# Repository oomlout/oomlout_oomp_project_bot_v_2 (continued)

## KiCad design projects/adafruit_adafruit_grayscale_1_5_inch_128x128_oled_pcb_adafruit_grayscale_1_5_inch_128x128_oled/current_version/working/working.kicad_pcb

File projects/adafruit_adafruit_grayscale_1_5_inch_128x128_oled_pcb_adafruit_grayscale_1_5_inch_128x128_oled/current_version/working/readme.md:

# adafruit_grayscale_1_5_inch_128x128_oled_pcb
 
## summary 
* id: adafruit_adafruit_grayscale_1_5_inch_128x128_oled_pcb_adafruit_grayscale_1_5_inch_128x128_oled
* user: adafruit
* name: adafruit_grayscale_1_5_inch_128x128_oled_pcb
* board: adafruit_grayscale_1_5_inch_128x128_oled
* repo: https://github.com/adafruit/Adafruit-Grayscale-1.5-inch-128x128-OLED-PCB

* src_file_repo_sch: 
* src_file_repo_sch_link: https://github.com/adafruit/Adafruit-Grayscale-1.5-inch-128x128-OLED-PCB/tree/main/
* full details link: https://github.com/oomlout/oomlout_oomp_project_bot_v_2/tree/main/projects/adafruit_adafruit_grayscale_1_5_inch_128x128_oled_pcb_adafruit_grayscale_1_5_inch_128x128_oled/current_version/working  

## schematic  
  
[schematic (pdf)](working_schematic.pdf) 

## pcb  

[board (pdf)](working.pdf)  

## working_bom
| Id | Designator | Footprint | Quantity | Designation | Supplier and ref |  | None | 
| --- | --- | --- | --- | --- | --- | --- | --- | 
| 1 | D4,D5,D3 | SOD-323 | 3 | 1N4148 |  |  | [''] | 
| 2 | SJ1,SJ2 | SOLDERJUMPER_CLOSEDWIRE | 2 |  |  |  | [''] | 
| 3 | C1,C8 | 0603-NO | 2 | 0.1uF |  |  | [''] | 
| 4 | R2,R3 | RESPACK_4X0603 | 2 | 10K |  |  | [''] | 
| 5 | U$25 | PCBFEAT-REV-040 | 1 |  |  |  | [''] | 
| 6 | Q2 | SOT363 | 1 | BSS138 |  |  | [''] | 
| 7 | U$20,U$31 | STEMMAQT | 2 |  |  |  | [''] | 
| 8 | FID3,FID4 | FIDUCIAL_1MM | 2 | FIDUCIAL_1MM |  |  | [''] | 
| 9 | C16,C3,C14,C7,C2,C15 | 0805-NO | 6 | 10uF |  |  | [''] | 
| 10 | C17 | 0603-NO | 1 | 1uF |  |  | [''] | 
| 11 | R9 | 0603-NO | 1 | 390K |  |  | [''] | 
| 12 | U$1,U$21,U$17,U$19 | MOUNTINGHOLE_2.5_PLATED | 4 | MOUNTINGHOLE2.5 |  |  | [''] | 
| 13 | D2 | SOD-123 | 1 | MBR120 |  |  | [''] | 
| 14 | R7,R1 | 0603-NO | 2 | 10K |  |  | [''] | 
| 15 | U2 | SOT23-5 | 1 | AP2112K-3.3 |  |  | [''] | 
| 16 | JP2 | 1X08_ROUND_70 | 1 |  |  |  | [''] | 
| 17 | IC5 | SOT23 | 1 | APX803 |  |  | [''] | 
| 18 | R6 | 0603-NO | 1 | 100K |  |  | [''] | 
| 19 | CONN4,CONN1 | JST_SH4 | 2 | STEMMA_I2C_QT |  |  | [''] | 
| 20 | U3 | SOT23-5@1 | 1 | FAN5331SX |  |  | [''] | 
| 21 | D1 | CHIPLED_0603_NOOUTLINE | 1 | GREEN |  |  | [''] | 
| 22 | U$8 | ADAFRUIT_5MM | 1 |  |  |  | [''] | 
| 23 | SJ3 | SOLDERJUMPER_ARROW_NOPASTE | 1 |  |  |  | [''] | 
| 24 | L1 | INDUCTOR_1007 | 1 | 10uH |  |  | [''] | 
| 25 | X1 | OLED_1.5IN_128X128MONO | 1 | OLED_1.5_128X128_MONO |  |  | [''] | 

## bom_schematic
| Ref | Qnty | Value | Cmp name | Footprint | Description | Vendor | DNP | 
| --- | --- | --- | --- | --- | --- | --- | --- | 
| C1, C8 | 2 | 0.1uF | CAP_CERAMIC0603_NO | working:0603-NO |  |  |  | 
| C2, C3, C7, C14, C15, C16 | 6 | 10uF | CAP_CERAMIC0805-NOOUTLINE | working:0805-NO |  |  |  | 
| C17 | 1 | 1uF | CAP_CERAMIC0603_NO | working:0603-NO |  |  |  | 
| CONN1, CONN4 | 2 | STEMMA_I2C_QT | STEMMA_I2C_QT | working:JST_SH4 |  |  |  | 
| D1 | 1 | GREEN | LED0603_NOOUTLINE | working:CHIPLED_0603_NOOUTLINE |  |  |  | 
| D2 | 1 | MBR120 | DIODESOD-123 | working:SOD-123 |  |  |  | 
| D3, D4, D5 | 3 | 1N4148 | DIODESOD-323 | working:SOD-323 |  |  |  | 
| FID3, FID4 | 2 | FIDUCIAL_1MM | FIDUCIAL_1MM | working:FIDUCIAL_1MM |  |  |  | 
| IC5 | 1 | APX803 | AXP083-SAG | working:SOT23 |  |  |  | 
| JP2 | 1 | HEADER-1X870MIL | HEADER-1X870MIL | working:1X08_ROUND_70 |  |  |  | 
| L1 | 1 | 10uH | INDUCTOR | working:INDUCTOR_1007 |  |  |  | 
| Q2 | 1 | BSS138 | MOSFET-N_DUAL | working:SOT363 |  |  |  | 
| R1, R7 | 2 | 10K | RESISTOR_0603_NOOUT | working:0603-NO |  |  |  | 
| R2, R3 | 2 | 10K | RESISTOR_4PACK | working:RESPACK_4X0603 |  |  |  | 
| R6 | 1 | 100K | RESISTOR_0603_NOOUT | working:0603-NO |  |  |  | 
| R9 | 1 | 390K | RESISTOR_0603_NOOUT | working:0603-NO |  |  |  | 
| SJ1, SJ2 | 2 | SOLDERJUMPERCLOSED | SOLDERJUMPERCLOSED | working:SOLDERJUMPER_CLOSEDWIRE |  |  |  | 
| SJ3 | 1 | SOLDERJUMPER | SOLDERJUMPER | working:SOLDERJUMPER_ARROW_NOPASTE |  |  |  | 
| U2 | 1 | AP2112K-3.3 | VREG_SOT23-5 | working:SOT23-5 |  |  |  | 
| U3 | 1 | FAN5331SX | FAN5331 | working:SOT23-5@1 |  |  |  | 
| U$1, U$17, U$19, U$21 | 4 | MOUNTINGHOLE2.5 | MOUNTINGHOLE2.5 | working:MOUNTINGHOLE_2.5_PLATED |  |  |  | 
| X1 | 1 | OLED_1.5_128X128_MONO | OLED_1.5_128X128_MONO | working:OLED_1.5IN_128X128MONO |  |  |  | 

## mounting_holes
| x | y | package | value | ref | size | 
| --- | --- | --- | --- | --- | --- | 
| 0.0 | 41.91 | MOUNTINGHOLE_2.5_PLATED | MOUNTINGHOLE2.5 | U$1 | m3 | 
| 30.48 | 41.91 | MOUNTINGHOLE_2.5_PLATED | MOUNTINGHOLE2.5 | U$17 | m3 | 
| 0.0 | 0.0 | MOUNTINGHOLE_2.5_PLATED | MOUNTINGHOLE2.5 | U$19 | m3 | 
| 30.48 | 0.0 | MOUNTINGHOLE_2.5_PLATED | MOUNTINGHOLE2.5 | U$21 | m3 |

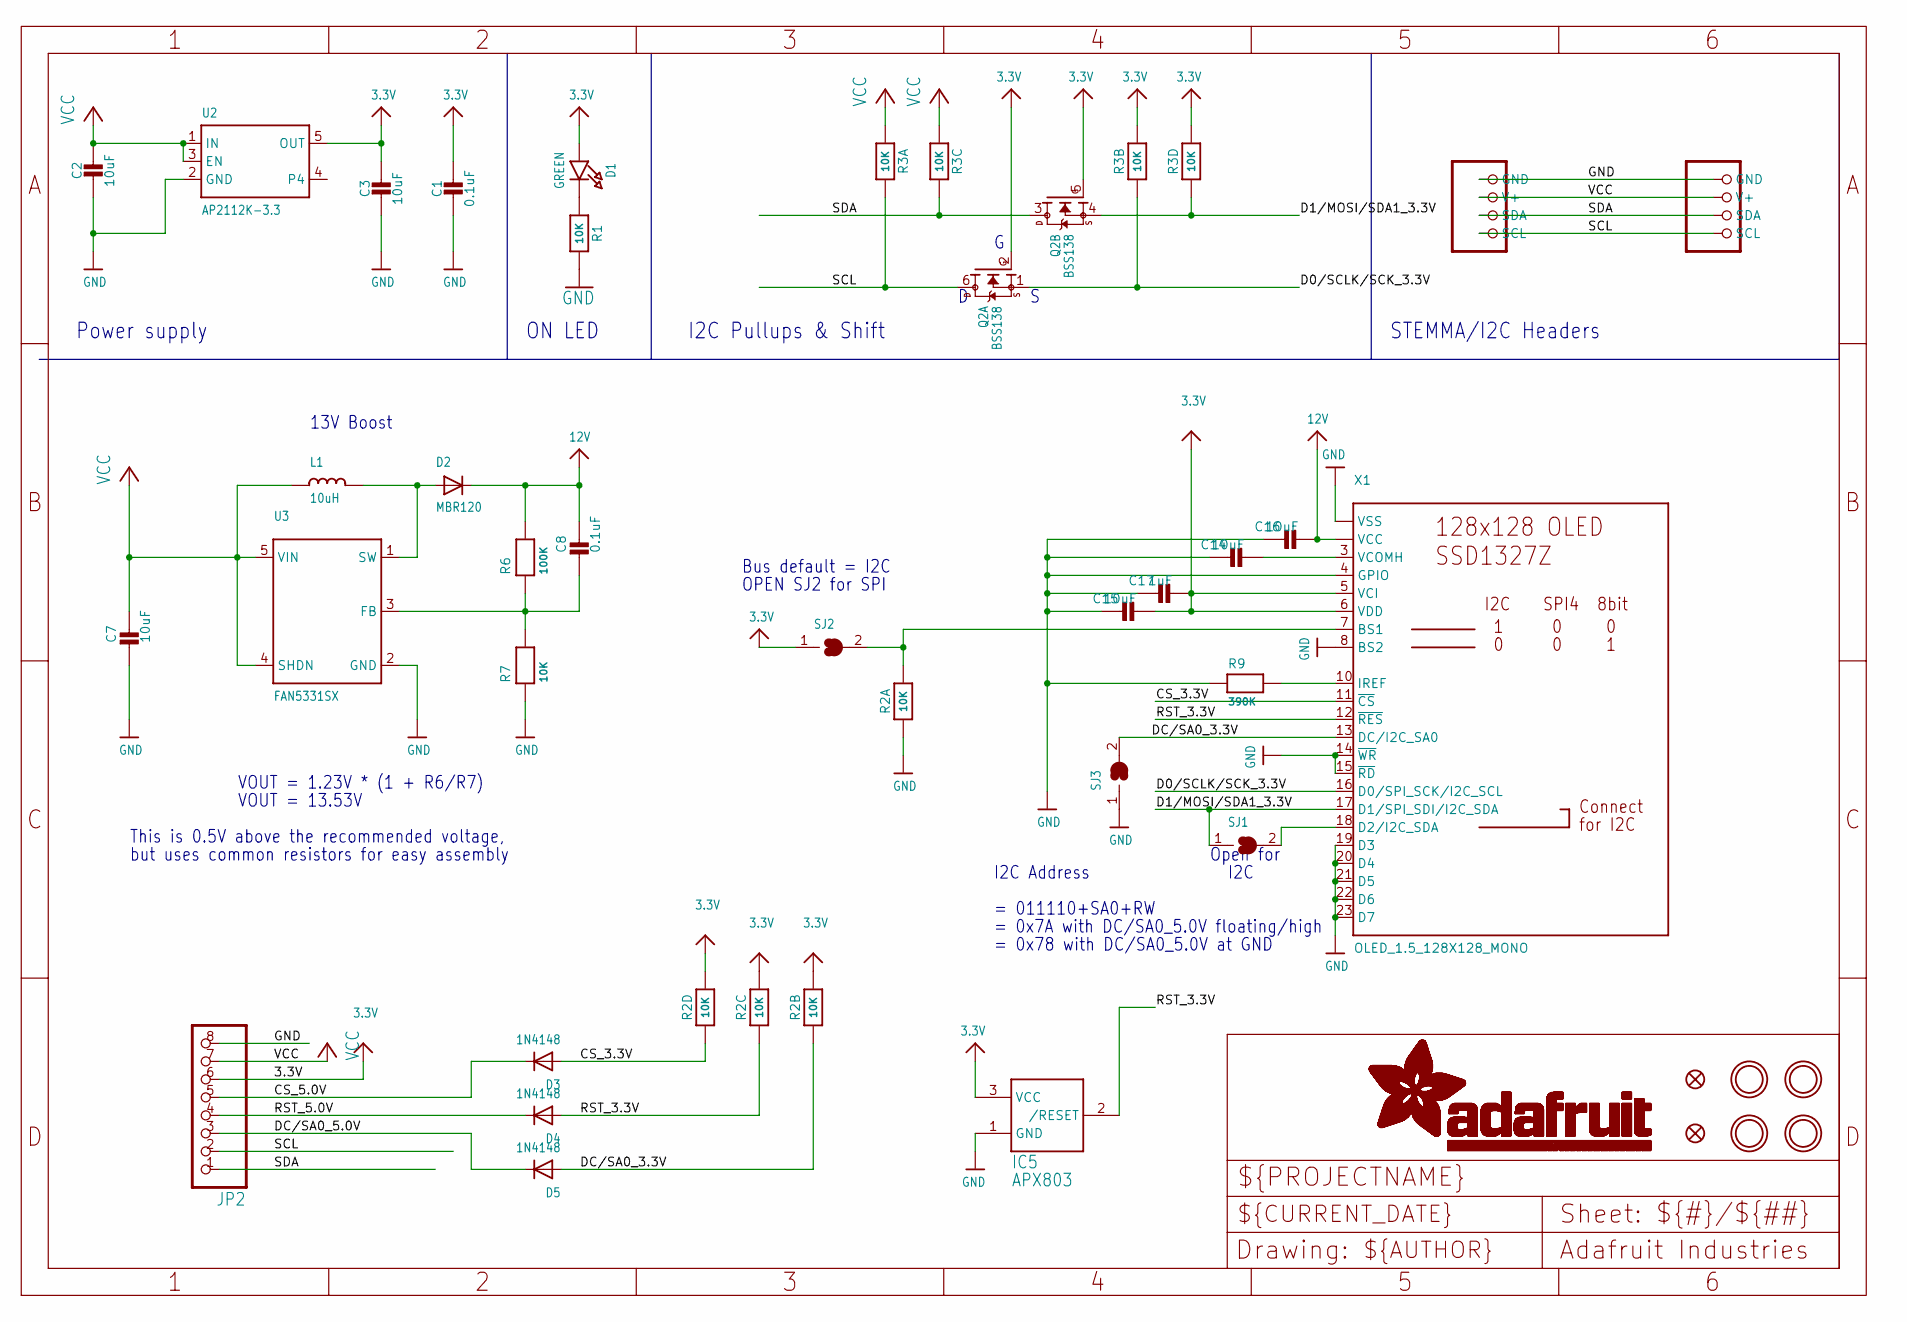
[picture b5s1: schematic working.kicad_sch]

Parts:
C1, C8: 0.1uF; 0603-NO
C2, C3, C7, C14, C15, C16: 10uF; 0805-NO
C17: 1uF; 0603-NO
CONN1, CONN4: STEMMA_I2C_QT; JST_SH4
D1: GREEN; CHIPLED_0603_NOOUTLINE
D2: MBR120; SOD-123
D3, D4, D5: 1N4148; SOD-323
FID3, FID4: FIDUCIAL_1MM
IC5: APX803; SOT23
JP2: HEADER-1X870MIL; 1X08_ROUND_70
L1: 10uH; INDUCTOR_1007
Q2: BSS138; SOT363
R1, R7: 10K; 0603-NO
R2, R3: 10K; RESPACK_4X0603
R6: 100K; 0603-NO
R9: 390K; 0603-NO
SJ1, SJ2: SOLDERJUMPERCLOSED; SOLDERJUMPER_CLOSEDWIRE
SJ3: SOLDERJUMPER; SOLDERJUMPER_ARROW_NOPASTE
U2: AP2112K-3.3; SOT23-5
U3: FAN5331SX; SOT23-5@1
U$1, U$17, U$19, U$21: MOUNTINGHOLE2.5; MOUNTINGHOLE_2.5_PLATED
X1: OLED_1.5_128X128_MONO; OLED_1.5IN_128X128MONO

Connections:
3.3V: C1.1, C3.1, C15.2, C17.2, D1.A, IC5.3 (VCC), JP2.6, Q2.2 (G), Q2.5 (G), R2.5 (2), R2.6 (2), R2.7 (2), R3.2 (1), R3.4 (1), SJ2.1, U2.5 (OUT), X1.5 (VCI), X1.6 (VDD)
12V: C8.1, C16.2, D2.C, R6.2, X1.2 (VCC), X1.24 (VCC)
CS_3.3V: D3.A, R2.4 (1), X1.11 (~CS)
CS_5.0V: D3.C, JP2.5
D0/SCLK/SCK_3.3V: Q2.1 (S), R3.7 (2), X1.16 (D0/SPI_SCK/I2C_SCL)
D1/MOSI/SDA1_3.3V: Q2.4 (S), R3.5 (2), SJ1.1, X1.17 (D1/SPI_SDI/I2C_SDA)
DC/SA0_3.3V: D5.A, R2.2 (1), SJ3.2, X1.13 (DC/I2C_SA0)
DC/SA0_5.0V: D5.C, JP2.3
GND: C1.2, C2.2, C3.2, C7.2, C14.1, C15.1, C16.1, C17.1, CONN1.1 (GND), CONN4.1 (GND), IC5.1 (GND), JP2.8, R1.2, R2.1, R7.1, R9.1, SJ3.1, U2.2 (GND), U3.2 (GND), X1.1 (VSS), X1.4 (GPIO), X1.8 (BS2), X1.9 (VSS), X1.14 (~WR), X1.15 (~RD), X1.19 (D3), X1.20 (D4), X1.21 (D5), X1.22 (D6), X1.23 (D7), X1.25 (VSS)
unnamed: D1.C, R1.1
unnamed: D2.A, L1.P$2 (2), U3.1 (SW)
unnamed: C8.2, R6.1, R7.2, U3.3 (FB)
unnamed: R2.8 (2), SJ2.2, X1.7 (BS1)
unnamed: R9.2, X1.10 (IREF)
unnamed: C14.2, X1.3 (VCOMH)
unnamed: SJ1.2, X1.18 (D2/I2C_SDA)
RST_3.3V: D4.A, IC5.2 (/RESET), R2.3 (1), X1.12 (~RES)
RST_5.0V: D4.C, JP2.4
SCL: CONN1.4 (SCL), CONN4.4 (SCL), JP2.2, Q2.6 (D), R3.8 (2)
SDA: CONN1.3 (SDA), CONN4.3 (SDA), JP2.1, Q2.3 (D), R3.6 (2)
VCC: C2.1, C7.1, CONN1.2 (V+), CONN4.2 (V+), JP2.7, L1.P$1 (1), R3.1, R3.3 (1), U2.1 (IN), U2.3 (EN), U3.4 (SHDN), U3.5 (VIN)

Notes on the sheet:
I2C
Open for
= 0x7A with DC/SA0_5.0V floating/high
This is 0.5V above the recommended voltage,
ON LED
but uses common resistors for easy assembly
I2C Pullups & Shift
= 011110+SA0+RW
= 0x78 with DC/SA0_5.0V at GND
Bus default = I2C
13V Boost
OPEN SJ2 for SPI
STEMMA/I2C Headers
VOUT = 13.53V
I2C Address
Power supply
VOUT = 1.23V * (1 + R6/R7)

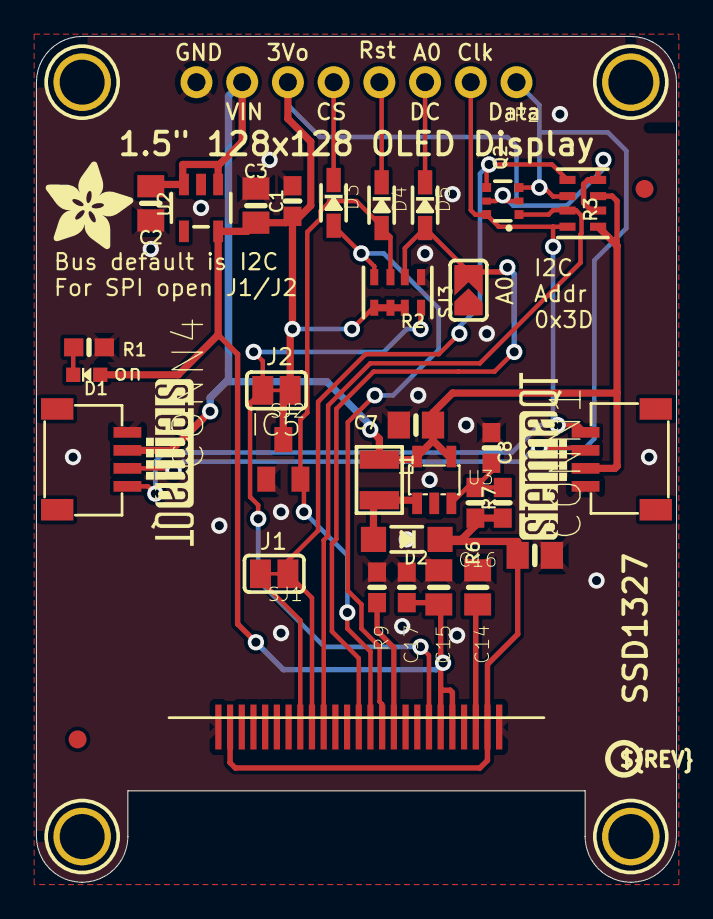
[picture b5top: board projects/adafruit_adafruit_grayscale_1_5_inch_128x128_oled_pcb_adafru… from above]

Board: 2 copper layers, 35.6 x 47.0 mm, 42 parts (1 on the bottom side), 21 nets.

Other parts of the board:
U$8: ADAFRUIT_5MM
U$20, U$31: STEMMAQT
U$25: PCBFEAT-REV-040

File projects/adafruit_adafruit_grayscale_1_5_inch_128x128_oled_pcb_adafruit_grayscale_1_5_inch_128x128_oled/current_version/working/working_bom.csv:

"Id";"Designator";"Footprint";"Quantity";"Designation";"Supplier and ref";
1;"D4,D5,D3";"SOD-323";3;"1N4148";;;
2;"SJ1,SJ2";"SOLDERJUMPER_CLOSEDWIRE";2;"";;;
3;"C1,C8";"0603-NO";2;"0.1uF";;;
4;"R2,R3";"RESPACK_4X0603";2;"10K";;;
5;"U$25";"PCBFEAT-REV-040";1;"";;;
6;"Q2";"SOT363";1;"BSS138";;;
7;"U$20,U$31";"STEMMAQT";2;"";;;
8;"FID3,FID4";"FIDUCIAL_1MM";2;"FIDUCIAL_1MM";;;
9;"C16,C3,C14,C7,C2,C15";"0805-NO";6;"10uF";;;
10;"C17";"0603-NO";1;"1uF";;;
11;"R9";"0603-NO";1;"390K";;;
12;"U$1,U$21,U$17,U$19";"MOUNTINGHOLE_2.5_PLATED";4;"MOUNTINGHOLE2.5";;;
13;"D2";"SOD-123";1;"MBR120";;;
14;"R7,R1";"0603-NO";2;"10K";;;
15;"U2";"SOT23-5";1;"AP2112K-3.3";;;
16;"JP2";"1X08_ROUND_70";1;"";;;
17;"IC5";"SOT23";1;"APX803";;;
18;"R6";"0603-NO";1;"100K";;;
19;"CONN4,CONN1";"JST_SH4";2;"STEMMA_I2C_QT";;;
20;"U3";"SOT23-5@1";1;"FAN5331SX";;;
21;"D1";"CHIPLED_0603_NOOUTLINE";1;"GREEN";;;
22;"U$8";"ADAFRUIT_5MM";1;"";;;
23;"SJ3";"SOLDERJUMPER_ARROW_NOPASTE";1;"";;;
24;"L1";"INDUCTOR_1007";1;"10uH";;;
25;"X1";"OLED_1.5IN_128X128MONO";1;"OLED_1.5_128X128_MONO";;;

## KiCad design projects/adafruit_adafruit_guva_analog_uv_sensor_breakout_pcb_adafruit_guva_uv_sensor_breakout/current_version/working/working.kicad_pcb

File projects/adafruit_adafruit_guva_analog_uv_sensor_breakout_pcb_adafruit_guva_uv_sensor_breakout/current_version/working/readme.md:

# adafruit_guva_analog_uv_sensor_breakout_pcb
 
## summary 
* id: adafruit_adafruit_guva_analog_uv_sensor_breakout_pcb_adafruit_guva_uv_sensor_breakout
* user: adafruit
* name: adafruit_guva_analog_uv_sensor_breakout_pcb
* board: adafruit_guva_uv_sensor_breakout
* repo: https://github.com/adafruit/Adafruit-GUVA-Analog-UV-Sensor-Breakout-PCB

* src_file_repo_sch: 
* src_file_repo_sch_link: https://github.com/adafruit/Adafruit-GUVA-Analog-UV-Sensor-Breakout-PCB/tree/master/
* full details link: https://github.com/oomlout/oomlout_oomp_project_bot_v_2/tree/main/projects/adafruit_adafruit_guva_analog_uv_sensor_breakout_pcb_adafruit_guva_uv_sensor_breakout/current_version/working  

## schematic  
  
[schematic (pdf)](working_schematic.pdf) 

## pcb  

[board (pdf)](working.pdf)  

## working_bom
| Id | Designator | Footprint | Quantity | Designation | Supplier and ref |  | None | 
| --- | --- | --- | --- | --- | --- | --- | --- | 
| 1 | U1 | SOT23-5 | 1 | MCP6001 |  |  | [''] | 
| 2 | R1 | 0805-NO | 1 | 1M |  |  | [''] | 
| 3 | JP2 | 1X03-CLEANBIG | 1 |  |  |  | [''] | 
| 4 | C2,C1 | 0805-NO | 2 | 0.1uF |  |  | [''] | 
| 5 | U2 | GUVA-S12SD | 1 | GUVA-S12SD |  |  | [''] | 
| 6 | U$7,U$8 | ADAFRUIT_2.5MM | 2 |  |  |  | [''] | 
| 7 | FID1,FID2 | FIDUCIAL_1MM | 2 | FIDUCIAL" |  |  | [''] | 
| 8 | U$6 | MOUNTINGHOLE_2.5_PLATED | 1 | MOUNTINGHOLE2.5 |  |  | [''] | 
| 9 | R2 | 0805-NO | 1 | 3.3K |  |  | [''] | 
| 10 | R3 | 0805-NO | 1 | 1K |  |  | [''] | 

## bom_schematic
| Ref | Qnty | Value | Cmp name | Footprint | Description | Vendor | DNP | 
| --- | --- | --- | --- | --- | --- | --- | --- | 
| C1, C2 | 2 | 0.1uF | CAP_CERAMIC0805-NOOUTLINE | working:0805-NO |  |  |  | 
| FID1, FID2 | 2 | FIDUCIAL"" | FIDUCIAL{dblquote}{dblquote} | working:FIDUCIAL_1MM |  |  |  | 
| JP2 | 1 | PINHD-1X3CB | PINHD-1X3CB | working:1X03-CLEANBIG |  |  |  | 
| R1 | 1 | 1M | RESISTOR0805_NOOUTLINE | working:0805-NO |  |  |  | 
| R2 | 1 | 3.3K | RESISTOR0805_NOOUTLINE | working:0805-NO |  |  |  | 
| R3 | 1 | 1K | RESISTOR0805_NOOUTLINE | working:0805-NO |  |  |  | 
| U1 | 1 | MCP6001 | OPAMP_SINGLESOT235 | working:SOT23-5 |  |  |  | 
| U2 | 1 | GUVA-S12SD | UV_GUVA-S12SD | working:GUVA-S12SD |  |  |  | 
| U$6 | 1 | MOUNTINGHOLE2.5 | MOUNTINGHOLE2.5 | working:MOUNTINGHOLE_2.5_PLATED |  |  |  | 

## mounting_holes
| x | y | package | value | ref | size | 
| --- | --- | --- | --- | --- | --- | 
| 0.0 | 0.0 | MOUNTINGHOLE_2.5_PLATED | MOUNTINGHOLE2.5 | U$6 | m3 |

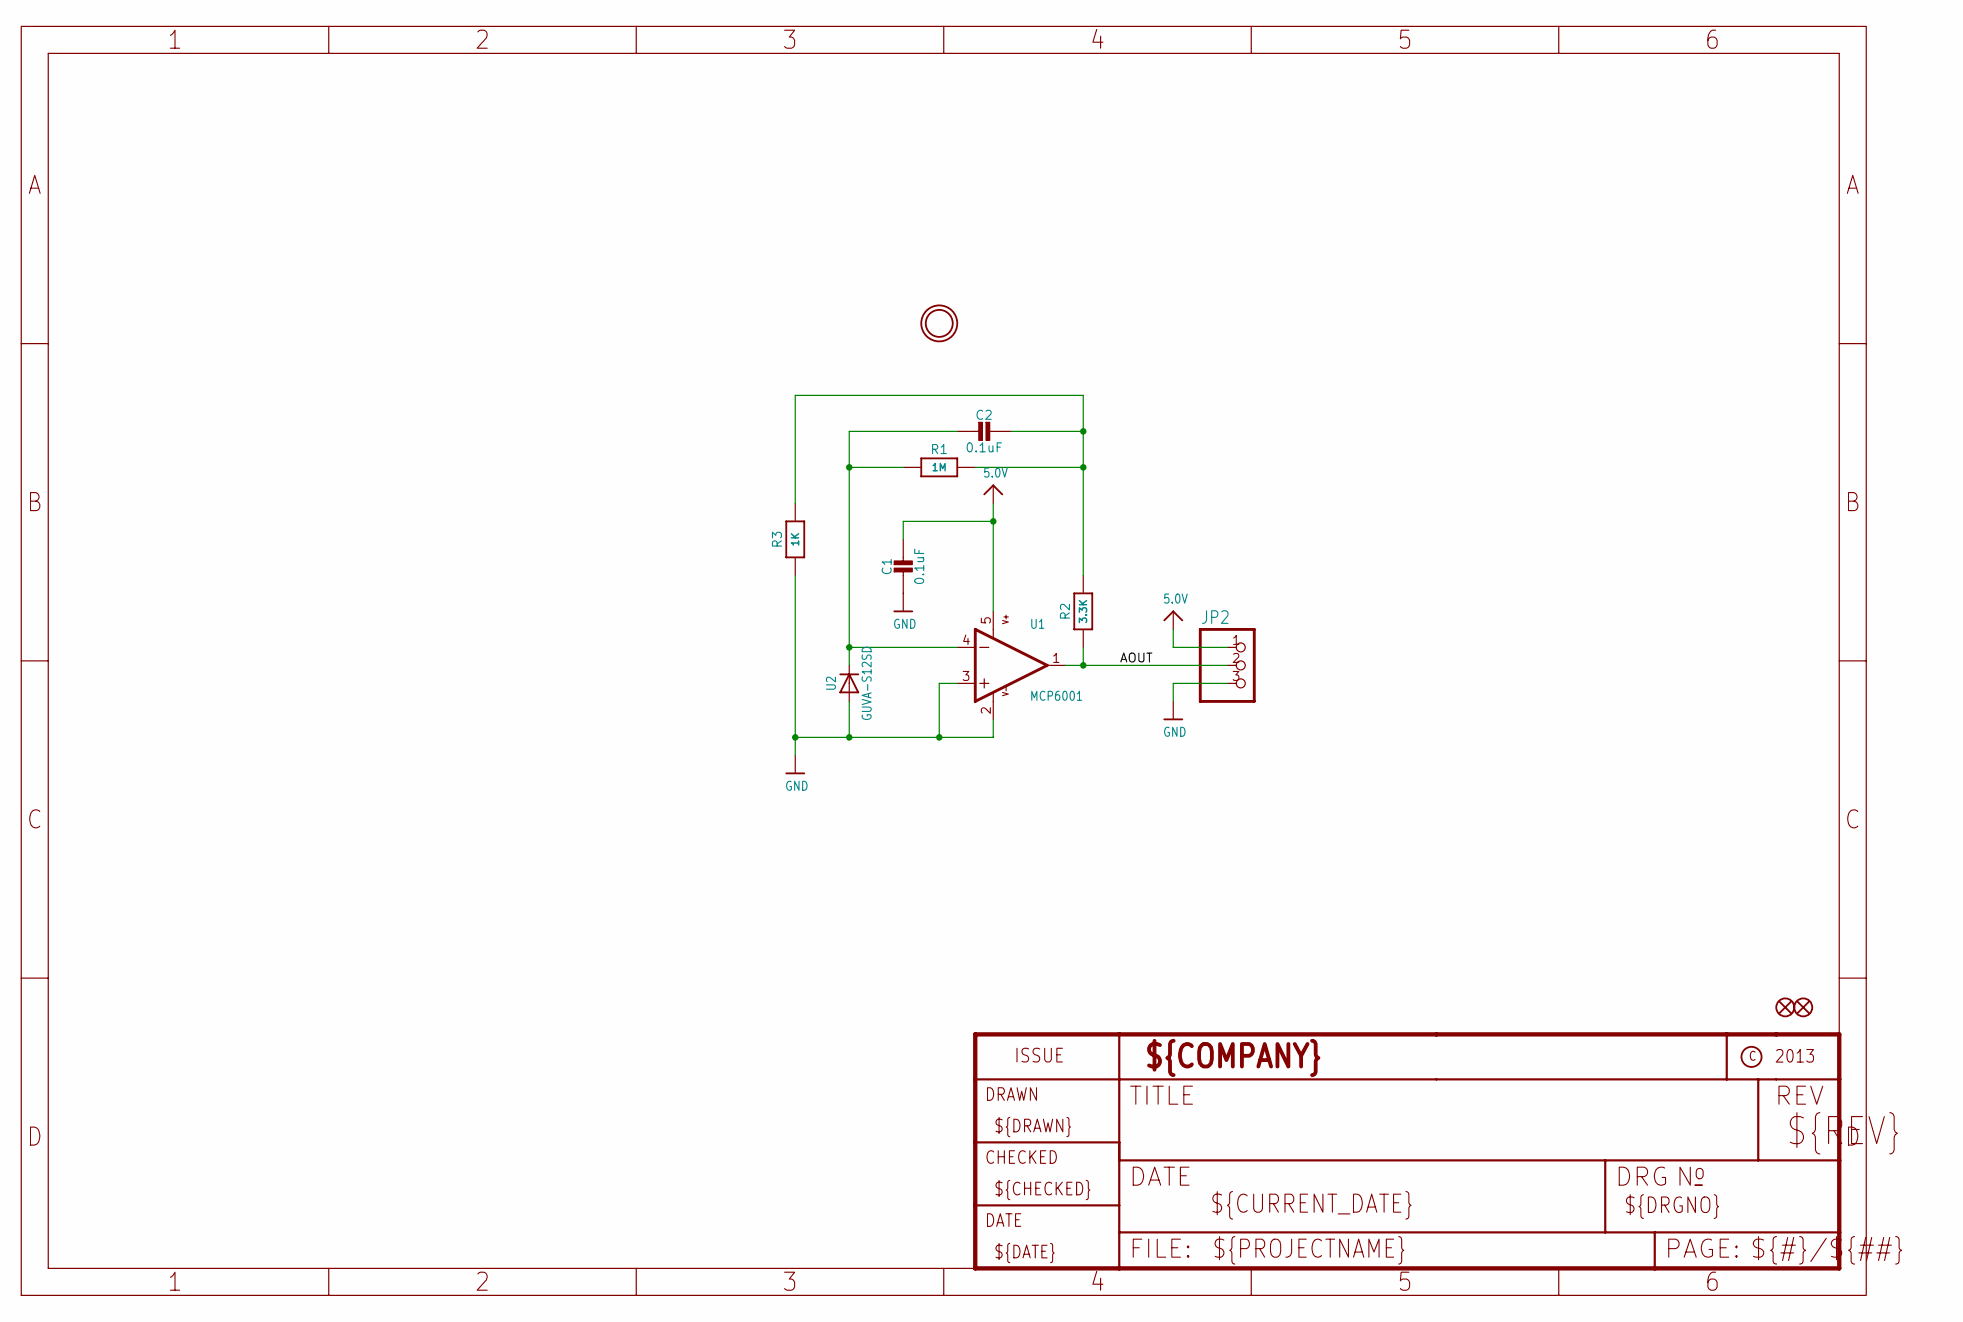
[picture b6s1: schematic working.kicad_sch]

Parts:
C1, C2: 0.1uF; 0805-NO
FID1, FID2: FIDUCIAL""; FIDUCIAL_1MM
JP2: PINHD-1X3CB; 1X03-CLEANBIG
R1: 1M; 0805-NO
R2: 3.3K; 0805-NO
R3: 1K; 0805-NO
U1: MCP6001; SOT23-5
U2: GUVA-S12SD
U$6: MOUNTINGHOLE2.5; MOUNTINGHOLE_2.5_PLATED

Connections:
5.0V: C1.1, JP2.1, U1.5 (V+)
AOUT: JP2.2, R2.1, U1.1 (OUT)
GND: C1.2, JP2.3, R3.1, U1.2 (V-), U1.3 (+IN), U2.A
unnamed: C2.1, R1.2, R2.2, R3.2
unnamed: C2.2, R1.1, U1.4 (-IN), U2.K (C)

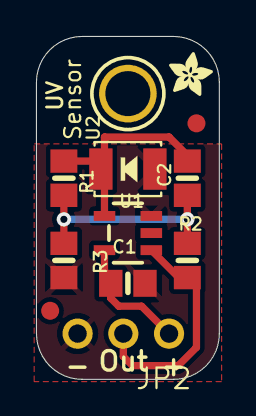
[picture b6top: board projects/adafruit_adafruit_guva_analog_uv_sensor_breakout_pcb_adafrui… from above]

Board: 2 copper layers, 10.2 x 19.0 mm, 13 parts (1 on the bottom side), 5 nets.

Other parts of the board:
U$7, U$8: ADAFRUIT_2.5MM

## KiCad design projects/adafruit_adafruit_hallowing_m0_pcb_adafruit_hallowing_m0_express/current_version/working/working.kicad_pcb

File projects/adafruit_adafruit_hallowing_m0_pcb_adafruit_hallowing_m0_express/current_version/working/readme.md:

# adafruit_hallowing_m0_pcb
 
## summary 
* id: adafruit_adafruit_hallowing_m0_pcb_adafruit_hallowing_m0_express
* user: adafruit
* name: adafruit_hallowing_m0_pcb
* board: adafruit_hallowing_m0_express
* repo: https://github.com/adafruit/Adafruit-Hallowing-M0-PCB

* src_file_repo_sch: 
* src_file_repo_sch_link: https://github.com/adafruit/Adafruit-Hallowing-M0-PCB/tree/master/
* full details link: https://github.com/oomlout/oomlout_oomp_project_bot_v_2/tree/main/projects/adafruit_adafruit_hallowing_m0_pcb_adafruit_hallowing_m0_express/current_version/working  

## schematic  
  
[schematic (pdf)](working_schematic.pdf) 

## pcb  

[board (pdf)](working.pdf)  

## working_bom
| Id | Designator | Footprint | Quantity | Designation | Supplier and ref |  | None | 
| --- | --- | --- | --- | --- | --- | --- | --- | 
| 1 | D1,D2 | SOD-323 | 2 | 3.6V |  |  | [''] | 
| 2 | R3,R8 | 0603-NO | 2 | 10K |  |  | [''] | 
| 3 | U1 | SOIC8_208MIL | 1 | 2MB Flash |  |  | [''] | 
| 4 | @HOLE3,@HOLE1,@HOLE2,@HOLE0 |  | 4 |  |  |  | [''] | 
| 5 | C9,C13,C7,C1,C4,C2,C14 | 0603-NO | 7 | 1uF |  |  | [''] | 
| 6 | R6,R5,R2 | 0603-NO | 3 | 1K |  |  | [''] | 
| 7 | MS1 | FEATHERWING_SMT_NOHOLES | 1 | FEATHERWING_SMTDUALNOHOLES |  |  | [''] | 
| 8 | LED1 | LED3535 | 1 | WS2812B3535 |  |  | [''] | 
| 9 | TP28,TP4 | PCB_ALLI | 2 | SEWTAPPCB_ALLIGATOR |  |  | [''] | 
| 10 | U2 | SOT23-5 | 1 | AP2112-3.3 |  |  | [''] | 
| 11 | U3 | SOT23-5 | 1 | MCP73831T-2ACI/OT |  |  | [''] | 
| 12 | X6 | JSTPH2 | 1 | CON_JST_PH_2PIN_MTPH2 |  |  | [''] | 
| 13 | NEOPIXEL0,PIR0 | JSTPH3 | 2 | JST PH 3 |  |  | [''] | 
| 14 | U$12 | HALLOWING_FRONT | 1 |  |  |  | [''] | 
| 15 | R13,R12 | 0603-NO | 2 | 100 |  |  | [''] | 
| 16 | C10,C15,C5 | 0805-NO | 3 | 10uF |  |  | [''] | 
| 17 | R9,R4 | RESPACK_4X0603 | 2 | 10K |  |  | [''] | 
| 18 | I2C0 | JSTPH4 | 1 | JST PH 4 |  |  | [''] | 
| 19 | Q2,Q1 | SOT23-R | 2 | DMG341 |  |  | [''] | 
| 20 | U$35,U$34 | FIDUCIAL_1MM | 2 | FIDUCIAL_1MM |  |  | [''] | 
| 21 | U4 | ALS-PT26-21C | 1 | ALS-PT21 |  |  | [''] | 
| 22 | SJ1 | SOLDERJUMPER_2WAY_OPEN_NOPASTE | 1 |  |  |  | [''] | 
| 23 | C11 | 0805_10MGAP | 1 | 10uF |  |  | [''] | 
| 24 | TP3,TP29 | PCB_ALLI_LONG | 2 | SEWTAP_ALLILONG |  |  | [''] | 
| 25 | IC4 | LGA16_3X3MM | 1 | LIS3DH |  |  | [''] | 
| 26 | U$4 | TQFN48_7MM | 1 | ATSAMD21G18_QFN |  |  | [''] | 
| 27 | R1 | RESPACK_4X0603 | 1 | 100K |  |  | [''] | 
| 28 | SW2 | EG1390 | 1 | Slide Switch |  |  | [''] | 
| 29 | CHG0 | CHIPLED_0805_NOOUTLINE | 1 | ORANGE |  |  | [''] | 
| 30 | VR2 | TRIMPOT_BOURNS_3303W | 1 | 10K trim |  |  | [''] | 
| 31 | TP5,TP1,TP2 | TESTPOINT_ROUND_1.5MM | 3 |  |  |  | [''] | 
| 32 | X3 | 4UCONN_20329_V2 | 1 | microUSB |  |  | [''] | 
| 33 | U$31,U$32 | MOUNTINGHOLE_2.5_PLATED | 2 | MOUNTINGHOLE2.5 |  |  | [''] | 
| 34 | U5 | MSOP8_0.65MM | 1 | PAM8302AASCR |  |  | [''] | 
| 35 | R7 | 0603-NO | 1 | 2.2K |  |  | [''] | 
| 36 | U$13 | 53398-0271 | 1 | CON_MOLEX_2P |  |  | [''] | 
| 37 | C3,C6 | 0805-NO | 2 | 10ÂµF |  |  | [''] | 
| 38 | Q3 | SOT23-WIDE | 1 | BSS138 |  |  | [''] | 
| 39 | C8 | 0805_10MGAP | 1 | 10ÂµF |  |  | [''] | 
| 40 | D4 | SOD-123 | 1 | MBR120 |  |  | [''] | 
| 41 | L0 | CHIPLED_0805_NOOUTLINE | 1 | RED |  |  | [''] | 
| 42 | SW1 | KMR2 | 1 | SPST_TACT-KMR2 |  |  | [''] | 
| 43 | X1 | JSTPH2 | 1 | JSTPH |  |  | [''] | 
| 44 | TFT0 | TFT_1.44IN_128_128 | 1 | DISP_LCD_ST7735_1.44IN |  |  | [''] | 
| 45 | U$8 | HALLOWING_BACK | 1 |  |  |  | [''] | 

## bom_schematic
| Ref | Qnty | Value | Cmp name | Footprint | Description | Vendor | DNP | 
| --- | --- | --- | --- | --- | --- | --- | --- | 
| C1, C2, C4, C7, C9, C13, C14 | 7 | 1uF | CAP_CERAMIC0603_NO | working:0603-NO |  |  |  | 
| C3, C6 | 2 | 10ÂµF | CAP_CERAMIC0805-NOOUTLINE | working:0805-NO |  |  |  | 
| C5, C10, C15 | 3 | 10uF | CAP_CERAMIC0805-NOOUTLINE | working:0805-NO |  |  |  | 
| C8 | 1 | 10ÂµF | CAP_CERAMIC0805_10MGAP | working:0805_10MGAP |  |  |  | 
| C11 | 1 | 10uF | CAP_CERAMIC0805_10MGAP | working:0805_10MGAP |  |  |  | 
| CHG0 | 1 | ORANGE | LED0805_NOOUTLINE | working:CHIPLED_0805_NOOUTLINE |  |  |  | 
| D1, D2 | 2 | 3.6V | DIODE-ZENERSOD323 | working:SOD-323 |  |  |  | 
| D4 | 1 | MBR120 | DIODE-SCHOTTKYSOD-123 | working:SOD-123 |  |  |  | 
| I2C0 | 1 | STEMMA_I2C_RASMT | STEMMA_I2C_RASMT | working:JSTPH4 |  |  |  | 
| IC4 | 1 | LIS3DH | ACCEL_LIS3DHTR | working:LGA16_3X3MM |  |  |  | 
| L0 | 1 | RED | LED0805_NOOUTLINE | working:CHIPLED_0805_NOOUTLINE |  |  |  | 
| LED1 | 1 | WS2812B3535 | WS2812B3535 | working:LED3535 |  |  |  | 
| MS1 | 1 | FEATHERWING_SMTDUALNOHOLES | FEATHERWING_SMTDUALNOHOLES | working:FEATHERWING_SMT_NOHOLES |  |  |  | 
| NEOPIXEL0 | 1 | JST PH 3 | CON_JST_PH_3PIN | working:JSTPH3 |  |  |  | 
| PIR0 | 1 | JST PH 3 | CON_JST_PH_3PIN | working:JSTPH3 |  |  |  | 
| Q1, Q2 | 2 | DMG341 | MOSFET-P | working:SOT23-R |  |  |  | 
| Q3 | 1 | BSS138 | MOSFET-NWIDE | working:SOT23-WIDE |  |  |  | 
| R1 | 1 | 100K | RESISTOR_4PACK | working:RESPACK_4X0603 |  |  |  | 
| R2, R5, R6 | 3 | 1K | RESISTOR_0603_NOOUT | working:0603-NO |  |  |  | 
| R3, R8 | 2 | 10K | RESISTOR_0603_NOOUT | working:0603-NO |  |  |  | 
| R4, R9 | 2 | 10K | RESISTOR_4PACK | working:RESPACK_4X0603 |  |  |  | 
| R7 | 1 | 2.2K | RESISTOR_0603_NOOUT | working:0603-NO |  |  |  | 
| R12, R13 | 2 | 100 | RESISTOR_0603_NOOUT | working:0603-NO |  |  |  | 
| SJ1 | 1 | SOLDERJUMPER_2WAY | SOLDERJUMPER_2WAY | working:SOLDERJUMPER_2WAY_OPEN_NOPASTE |  |  |  | 
| SW1 | 1 | SPST_TACT-KMR2 | SPST_TACT-KMR2 | working:KMR2 |  |  |  | 
| SW2 | 1 | Slide Switch | SWITCH_DPDTEG1390 | working:EG1390 |  |  |  | 
| TFT0 | 1 | DISP_LCD_ST7735_1.44IN | DISP_LCD_ST7735_1.44IN | working:TFT_1.44IN_128_128 |  |  |  | 
| TP1, TP2, TP5 | 3 | TESTPOINTROUND1.5MM | TESTPOINTROUND1.5MM | working:TESTPOINT_ROUND_1.5MM |  |  |  | 
| TP3, TP29 | 2 | SEWTAP_ALLILONG | SEWTAP_ALLILONG | working:PCB_ALLI_LONG |  |  |  | 
| TP4, TP28 | 2 | SEWTAPPCB_ALLIGATOR | SEWTAPPCB_ALLIGATOR | working:PCB_ALLI |  |  |  | 
| U1 | 1 | 2MB Flash | SPIFLASH_8PIN208MIL | working:SOIC8_208MIL |  |  |  | 
| U2 | 1 | AP2112-3.3 | VREG_SOT23-5 | working:SOT23-5 |  |  |  | 
| U3 | 1 | MCP73831T-2ACI/OT | MCP73831/2 | working:SOT23-5 |  |  |  | 
| U4 | 1 | ALS-PT21 | PHOTOTRANSISTOR_PT26-21C | working:ALS-PT26-21C |  |  |  | 
| U5 | 1 | PAM8302AASCR | AUDIOAMP_PAM8302A | working:MSOP8_0.65MM |  |  |  | 
| U$4 | 1 | ATSAMD21G_QFN | ATSAMD21G_QFN | working:TQFN48_7MM |  |  |  | 
| U$13 | 1 | CON_MOLEX_2P | CON_MOLEX_2P | working:53398-0271 |  |  |  | 
| U$31, U$32 | 2 | MOUNTINGHOLE2.5 | MOUNTINGHOLE2.5 | working:MOUNTINGHOLE_2.5_PLATED |  |  |  | 
| U$34, U$35 | 2 | FIDUCIAL_1MM | FIDUCIAL_1MM | working:FIDUCIAL_1MM |  |  |  | 
| VR2 | 1 | 10K trim | TRIMPOT3303W/X | working:TRIMPOT_BOURNS_3303W |  |  |  | 
| X1 | 1 | JSTPH | CON_JST_PH_2PIN | working:JSTPH2 |  |  |  | 
| X3 | 1 | microUSB | USB_MICRO_20329_V2 | working:4UCONN_20329_V2 |  |  |  | 
| X6 | 1 | CON_JST_PH_2PIN_MTPH2 | CON_JST_PH_2PIN_MTPH2 | working:JSTPH2 |  |  |  | 

## mounting_holes
| x | y | package | value | ref | size | 
| --- | --- | --- | --- | --- | --- | 
| 17.78 | 0.0 | MOUNTINGHOLE_2.5_PLATED | MOUNTINGHOLE2.5 | U$31 | m3 | 
| 0.0 | 0.0 | MOUNTINGHOLE_2.5_PLATED | MOUNTINGHOLE2.5 | U$32 | m3 |

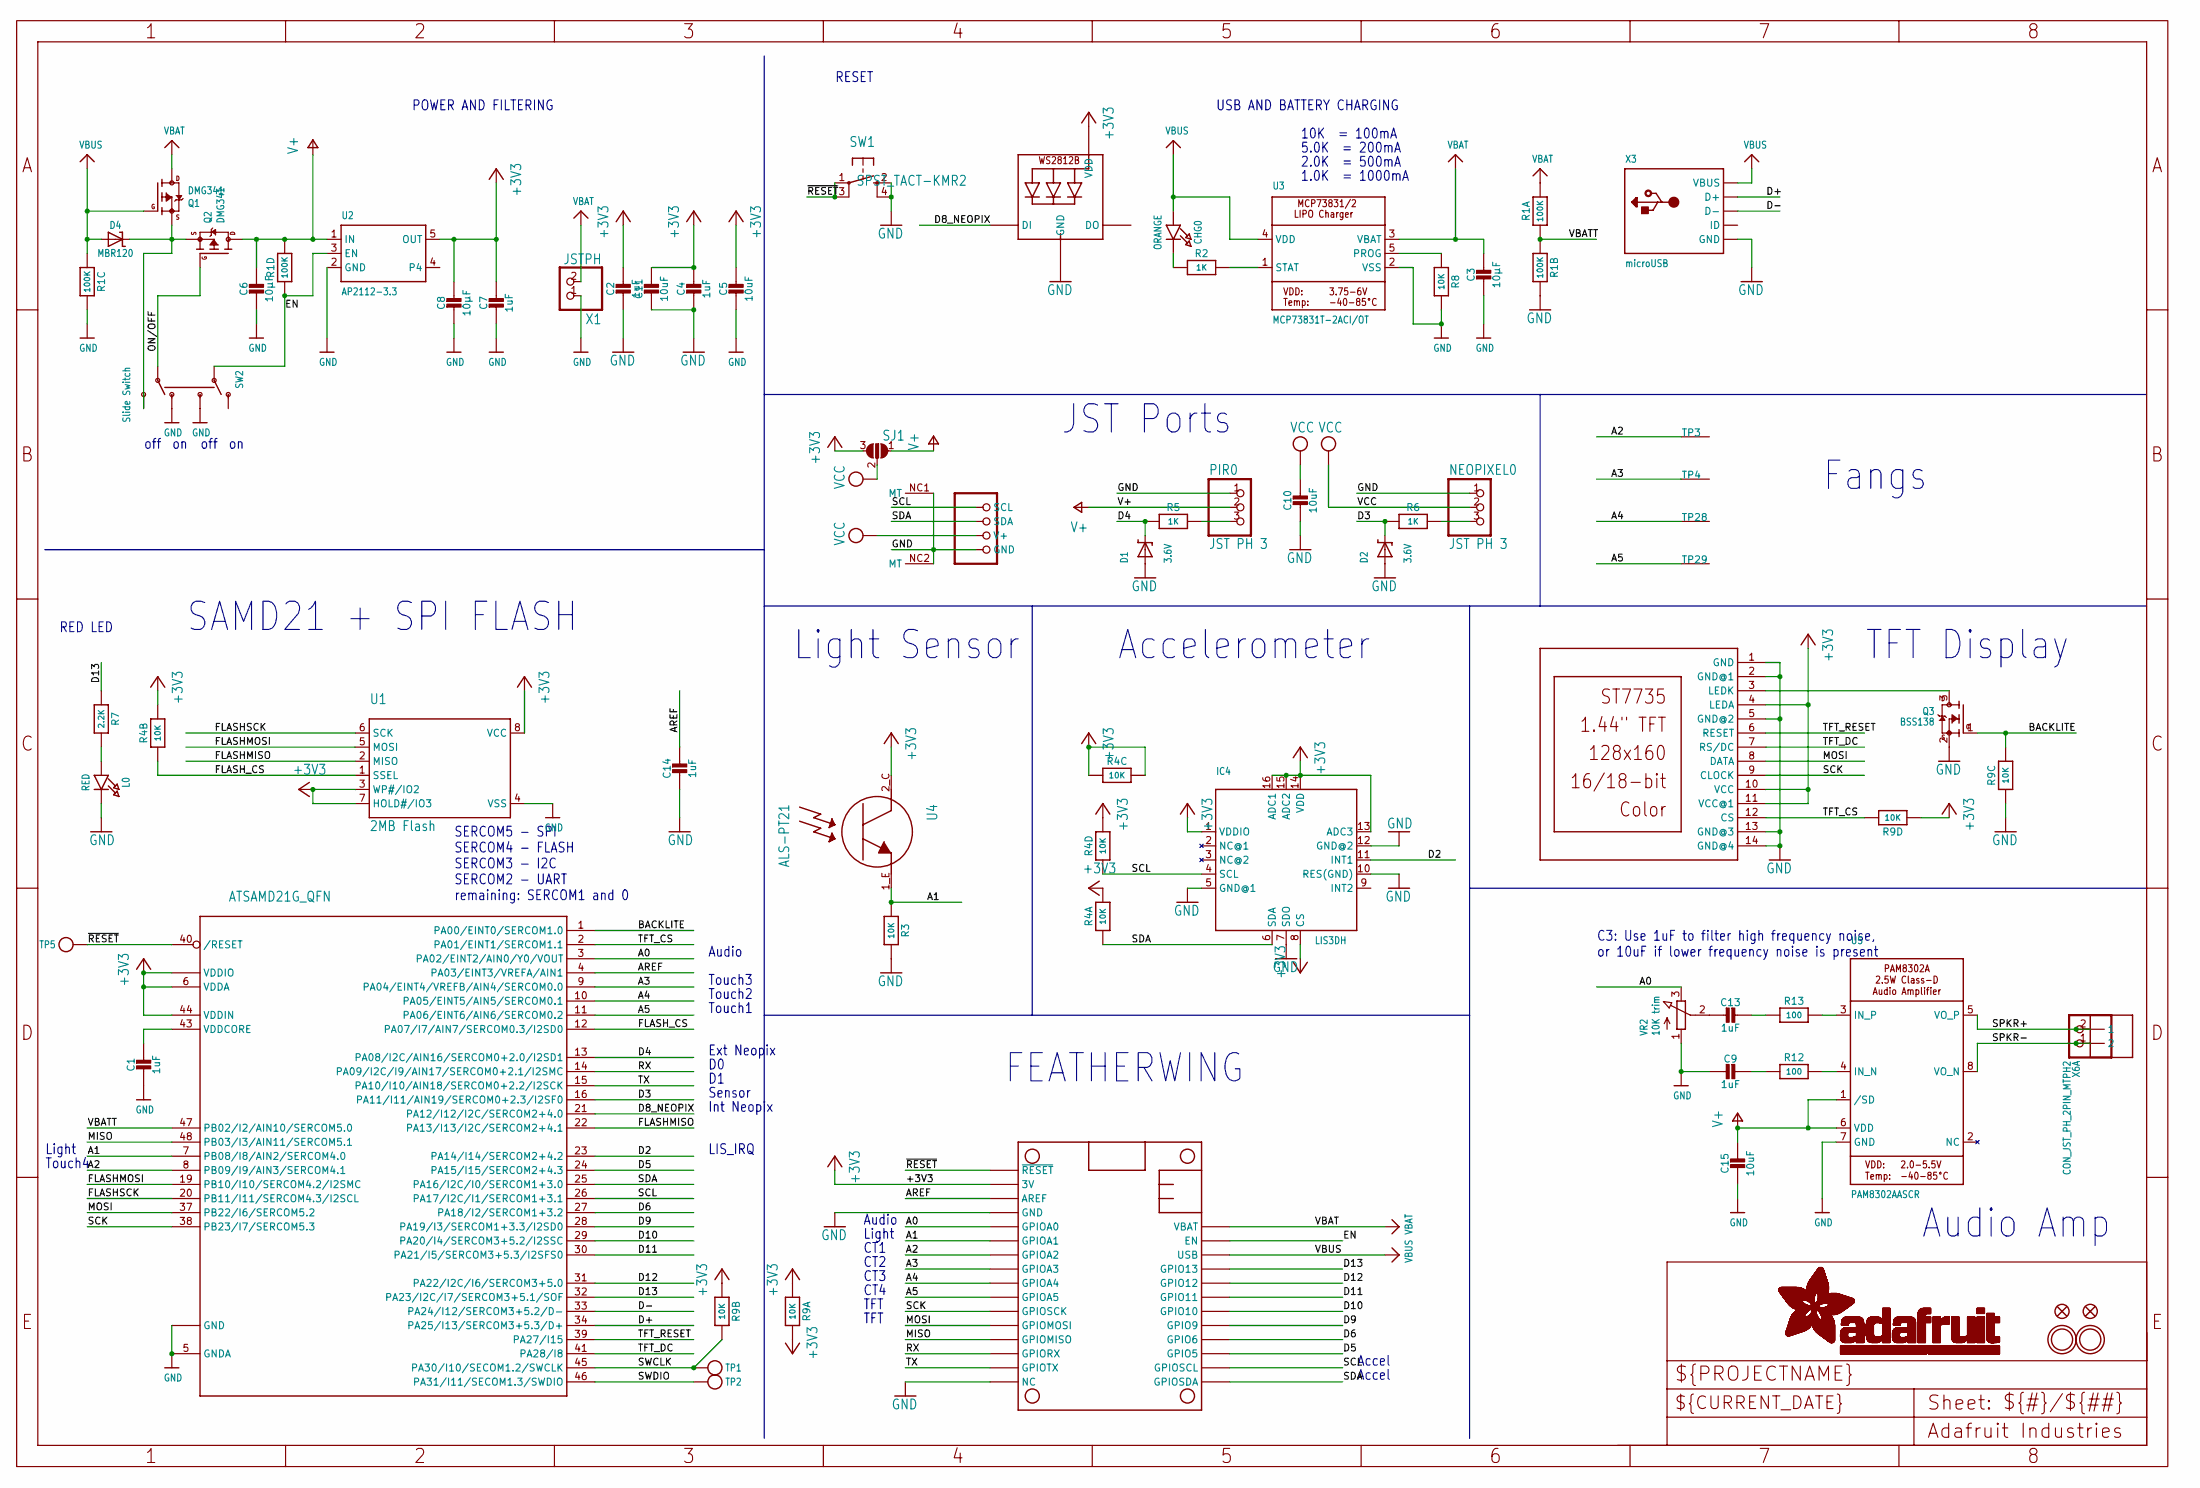
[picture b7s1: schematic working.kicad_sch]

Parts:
C1, C2, C4, C7, C9, C13, C14: 1uF; 0603-NO
C3, C6: 10µF; 0805-NO
C5, C10, C15: 10uF; 0805-NO
C8: 10µF; 0805_10MGAP
C11: 10uF; 0805_10MGAP
CHG0: ORANGE; CHIPLED_0805_NOOUTLINE
D1, D2: 3.6V; SOD-323
D4: MBR120; SOD-123
I2C0: STEMMA_I2C_RASMT; JSTPH4
IC4: LIS3DH; LGA16_3X3MM
L0: RED; CHIPLED_0805_NOOUTLINE
LED1: WS2812B3535; LED3535
MS1: FEATHERWING_SMTDUALNOHOLES; FEATHERWING_SMT_NOHOLES
NEOPIXEL0: JST PH 3; JSTPH3
PIR0: JST PH 3; JSTPH3
Q1, Q2: DMG341; SOT23-R
Q3: BSS138; SOT23-WIDE
R1: 100K; RESPACK_4X0603
R2, R5, R6: 1K; 0603-NO
R3, R8: 10K; 0603-NO
R4, R9: 10K; RESPACK_4X0603
R7: 2.2K; 0603-NO
R12, R13: 100; 0603-NO
SJ1: SOLDERJUMPER_2WAY; SOLDERJUMPER_2WAY_OPEN_NOPASTE
SW1: SPST_TACT-KMR2; KMR2
SW2: Slide Switch; EG1390
TFT0: DISP_LCD_ST7735_1.44IN; TFT_1.44IN_128_128
TP1, TP2, TP5: TESTPOINTROUND1.5MM; TESTPOINT_ROUND_1.5MM
TP3, TP29: SEWTAP_ALLILONG; PCB_ALLI_LONG
TP4, TP28: SEWTAPPCB_ALLIGATOR; PCB_ALLI
U1: 2MB Flash; SOIC8_208MIL
U2: AP2112-3.3; SOT23-5
U3: MCP73831T-2ACI/OT; SOT23-5
U4: ALS-PT21; ALS-PT26-21C
U5: PAM8302AASCR; MSOP8_0.65MM
U$4: ATSAMD21G_QFN; TQFN48_7MM
U$13: CON_MOLEX_2P; 53398-0271
U$31, U$32: MOUNTINGHOLE2.5; MOUNTINGHOLE_2.5_PLATED
U$34, U$35: FIDUCIAL_1MM
VR2: 10K trim; TRIMPOT_BOURNS_3303W
X1: JSTPH; JSTPH2
X3: microUSB; 4UCONN_20329_V2
X6: CON_JST_PH_2PIN_MTPH2; JSTPH2

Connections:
+3V3: C2.1, C4.1, C5.1, C7.1, C8.1, C11.1, IC4.1 (VDDIO), IC4.8 (CS), IC4.13 (ADC3), IC4.14 (VDD), IC4.15 (ADC2), IC4.16 (ADC1), LED1.2 (VDD), MS1.2 (3V), MS1.2' (3V), R4.3 (1), R4.5 (2), R4.6 (2), R4.7 (2), R4.8 (2), R9.1, R9.2 (1), R9.4 (1), R9.8 (2), SJ1.3, TFT0.4 (LEDA), TFT0.10 (VCC), TFT0.11 (VCC@1), U1.3 (WP#/IO2), U1.7 (HOLD#/IO3), U1.8 (VCC), U2.5 (OUT), U4.2_C (C), U$4.6 (VDDA), U$4.17 (VDDIO), U$4.36 (VDDIO), U$4.44 (VDDIN)
A0: MS1.5 (GPIOA0), MS1.5' (GPIOA0), U$4.3 (PA02/EINT2/AIN0/Y0/VOUT), VR2.3 (E)
A1: MS1.6 (GPIOA1), MS1.6' (GPIOA1), R3.2, U4.1_E (E), U$4.7 (PB08/I8/AIN2/SERCOM4.0)
A2: MS1.7 (GPIOA2), MS1.7' (GPIOA2), TP3.P$1, U$4.8 (PB09/I9/AIN3/SERCOM4.1)
A3: MS1.8 (GPIOA3), MS1.8' (GPIOA3), TP4.P$1, U$4.9 (PA04/EINT4/VREFB/AIN4/SERCOM0.0)
A4: MS1.9 (GPIOA4), MS1.9' (GPIOA4), TP28.P$1, U$4.10 (PA05/EINT5/AIN5/SERCOM0.1)
A5: MS1.10 (GPIOA5), MS1.10' (GPIOA5), TP29.P$1, U$4.11 (PA06/EINT6/AIN6/SERCOM0.2)
AREF: C14.1, MS1.3 (AREF), MS1.3' (AREF), U$4.4 (PA03/EINT3/VREFA/AIN1)
BACKLITE: Q3.1 (G), R9.6 (2), U$4.1 (PA00/EINT0/SERCOM1.0)
CHG_LED: R2.2, U3.1 (STAT)
CHG_RATE: R8.1, U3.5 (PROG)
D2: IC4.11 (INT1), U$4.23 (PA14/I14/SERCOM2+4.2)
D3: D2.C, R6.2, U$4.16 (PA11/I11/AIN19/SERCOM0+2.3/I2SF0)
D4: D1.C, R5.2, U$4.13 (PA08/I2C/AIN16/SERCOM0+2.0/I2SD1)
D5: MS1.19 (GPIO5), MS1.19' (GPIO5), U$4.24 (PA15/I15/SERCOM2+4.3)
D6: MS1.20 (GPIO6), MS1.20' (GPIO6), U$4.27 (PA18/I2/SERCOM1+3.2)
D8_NEOPIX: LED1.1 (DI), U$4.21 (PA12/I12/I2C/SERCOM2+4.0)
D9: MS1.21 (GPIO9), MS1.21' (GPIO9), U$4.28 (PA19/I3/SERCOM1+3.3/I2SD0)
D10: MS1.22 (GPIO10), MS1.22' (GPIO10), U$4.29 (PA20/I4/SERCOM3+5.2/I2SSC)
D11: MS1.23 (GPIO11), MS1.23' (GPIO11), U$4.30 (PA21/I5/SERCOM3+5.3/I2SFS0)
D12: MS1.24 (GPIO12), MS1.24' (GPIO12), U$4.31 (PA22/I2C/I6/SERCOM3+5.0)
D13: MS1.25 (GPIO13), MS1.25' (GPIO13), R7.1, U$4.32 (PA23/I2C/I7/SERCOM3+5.1/SOF)
D+: U$4.34 (PA25/I13/SERCOM3+5.3/D+), X3.D+
D-: U$4.33 (PA24/I12/SERCOM3+5.2/D-), X3.D-
EN: MS1.27 (EN), MS1.27' (EN), R1.4 (1), SW2.P1, U2.3 (EN)
FLASHMISO: U1.2 (MISO), U$4.22 (PA13/I13/I2C/SERCOM2+4.1)
FLASHMOSI: U1.5 (MOSI), U$4.19 (PB10/I10/SERCOM4.2/I2SMC)
FLASHSCK: U1.6 (SCK), U$4.20 (PB11/I11/SERCOM4.3/I2SCL)
FLASH_CS: R4.2 (1), U1.1 (SSEL), U$4.12 (PA07/I7/AIN7/SERCOM0.3/I2SD0)
GND: C1.2, C2.2, C3.2, C4.2, C5.2, C6.2, C7.2, C8.2, C9.2, C10.2, C11.2, C14.2, C15.2, D1.A, D2.A, I2C0.1 (GND), I2C0.NC1 (MT), I2C0.NC2 (MT), IC4.5 (GND@1), IC4.7 (SDO), IC4.10 (RES(GND)), IC4.12 (GND@2), L0.C, LED1.4 (GND), MS1.4 (GND), MS1.4' (GND), MS1.16 (NC), MS1.16' (NC), NEOPIXEL0.1, PIR0.1, Q3.2 (S), R1.6 (2), R1.7 (2), R3.1, R8.2, R9.3 (1), SW1.2 (S), SW1.4 (S1), SW2.O2, SW2.S1, TFT0.1 (GND), TFT0.2 (GND@1), TFT0.5 (GND@2), TFT0.13 (GND@3), TFT0.14 (GND@4), U1.4 (VSS), U2.2 (GND), U3.2 (VSS), U5.7 (GND), U$4.5 (GNDA), U$4.18 (GND), U$4.35 (GND), U$4.42 (GND), U$4.THERMAL (GND), VR2.1 (A), X1.1, X3.BASE@1 (GND), X3.BASE@2 (GND), X3.GND, X3.SPRT@1 (GND), X3.SPRT@2 (GND), X3.SPRT@3 (GND), X3.SPRT@4 (GND)
MISO: MS1.13 (GPIOMISO), MS1.13' (GPIOMISO), U$4.48 (PB03/I3/AIN11/SERCOM5.1)
MOSI: MS1.12 (GPIOMOSI), MS1.12' (GPIOMOSI), TFT0.8 (DATA), U$4.37 (PB22/I6/SERCOM5.2)
unnamed: CHG0.C, R2.1
unnamed: L0.A, R7.2
unnamed: Q3.3 (D), TFT0.3 (LEDK)
unnamed: D4.C, Q1.2 (S), Q2.2 (S), SW2.S2
unnamed: R12.2, U5.4 (IN_N)
unnamed: R13.2, U5.3 (IN_P)
unnamed: C9.1, R12.1
unnamed: C13.1, R13.1
unnamed: C13.2, VR2.2 (S)
NEOPIXELOUT: NEOPIXEL0.3, R6.1
ON/OFF: Q2.1 (G), SW2.P2
RX: MS1.14 (GPIORX), MS1.14' (GPIORX), U$4.14 (PA09/I2C/I9/AIN17/SERCOM0+2.1/I2SMC)
SCK: MS1.11 (GPIOSCK), MS1.11' (GPIOSCK), TFT0.9 (CLOCK), U$4.38 (PB23/I7/SERCOM5.3)
SCL: I2C0.4 (SCL), IC4.4 (SCL), MS1.18 (GPIOSCL), MS1.18' (GPIOSCL), R4.4 (1), U$4.26 (PA17/I2C/I1/SERCOM1+3.1)
SDA: I2C0.3 (SDA), IC4.6 (SDA), MS1.17 (GPIOSDA), MS1.17' (GPIOSDA), R4.1, U$4.25 (PA16/I2C/I0/SERCOM1+3.0)
SENSORIN: PIR0.3, R5.1
SPKR+: U5.5 (VO_P), U$13.1, X6.2
SPKR-: U5.8 (VO_N), U$13.2, X6.1
SWCLK: R9.7 (2), TP1.P$1, U$4.45 (PA30/I10/SECOM1.2/SWCLK)
SWDIO: TP2.P$1, U$4.46 (PA31/I11/SECOM1.3/SWDIO)
TFT_CS: R9.5 (2), TFT0.12 (CS), U$4.2 (PA01/EINT1/SERCOM1.1)
TFT_DC: TFT0.7 (RS/DC), U$4.41 (PA28/I8)
TFT_RESET: TFT0.6 (RESET), U$4.39 (PA27/I15)
TX: MS1.15 (GPIOTX), MS1.15' (GPIOTX), U$4.15 (PA10/I10/AIN18/SERCOM0+2.2/I2SCK)
V+: C6.1, C15.1, PIR0.2, Q2.3 (D), R1.5 (2), SJ1.1, U2.1 (IN), U5.1 (/SD), U5.6 (VDD)
VBAT: C3.1, MS1.28 (VBAT), MS1.28' (VBAT), Q1.3 (D), R1.8 (2), U3.3 (VBAT), X1.2
VBATT: R1.1, R1.2 (1), U$4.47 (PB02/I2/AIN10/SERCOM5.0)
VBUS: CHG0.A, D4.A, MS1.26 (USB), MS1.26' (USB), Q1.1 (G), R1.3 (1), U3.4 (VDD), X3.VBUS
VCC: C10.1, I2C0.2 (V+), NEOPIXEL0.2, SJ1.2
VDDCORE: C1.1, U$4.43 (VDDCORE)
~RESET: MS1.1 (~RESET), MS1.1' (~RESET), SW1.1, SW1.3 (P1), TP5.P$1, U$4.40 (/RESET)

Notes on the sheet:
C3: Use 1uF to filter high frequency noise, or 10uF if lower frequency noise is present
Fangs
CT1
Audio
off
Audio Amp
Ext Neopix
CT3
LIS_IRQ
CT2
Touch1
Touch3
POWER AND FILTERING
Touch4
TFT
2.0K = 500mA
Accel
Sensor
USB AND BATTERY CHARGING
SAMD21 + SPI FLASH
RESET
Int Neopix
10K = 100mA
Light Sensor
FEATHERWING
CT4
Light
JST Ports
5.0K = 200mA
RED LED
SERCOM5 - SPI SERCOM4 - FLASH SERCOM3 - I2C SERCOM2 - UART remaining: SERCOM1 and 0
TFT Display
Accelerometer
1.0K = 1000mA
Touch2

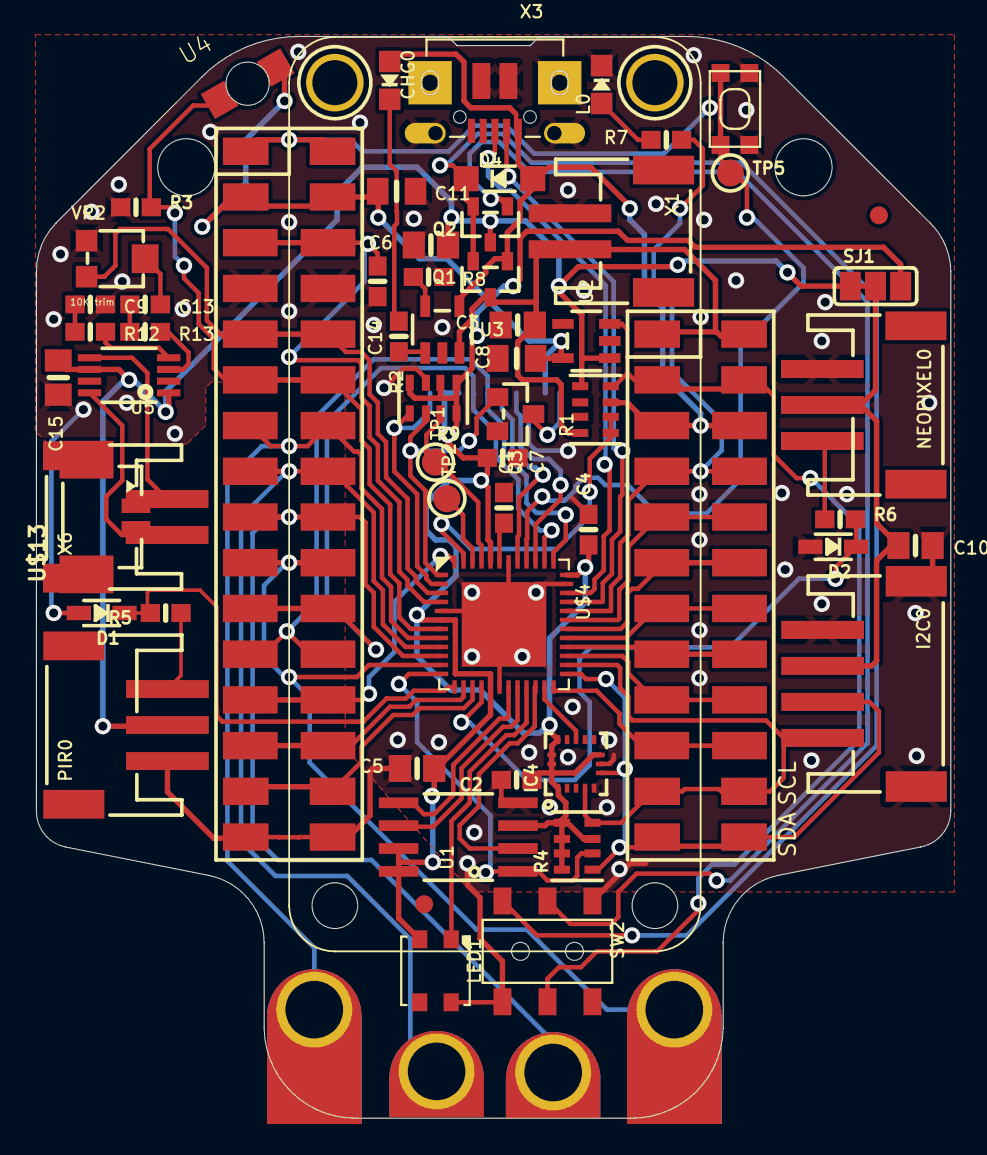
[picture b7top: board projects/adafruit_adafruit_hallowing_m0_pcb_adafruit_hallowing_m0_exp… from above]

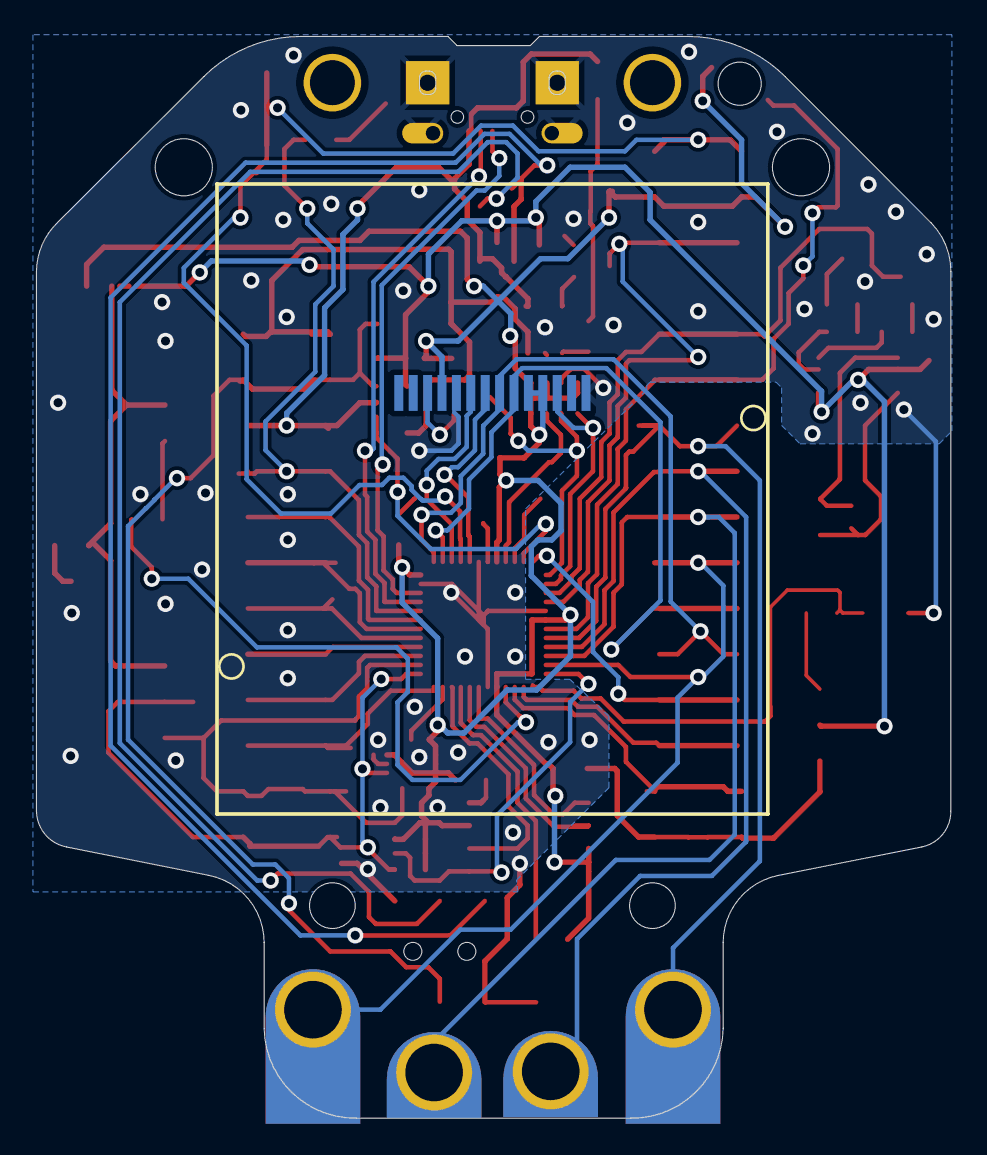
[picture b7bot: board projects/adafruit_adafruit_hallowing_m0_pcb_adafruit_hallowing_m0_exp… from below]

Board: 2 copper layers, 50.8 x 60.1 mm, 71 parts (2 on the bottom side), 63 nets.

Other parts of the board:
@HOLE0, @HOLE1, @HOLE2, @HOLE3: (no value)
U$8: HALLOWING_BACK
U$12: HALLOWING_FRONT
